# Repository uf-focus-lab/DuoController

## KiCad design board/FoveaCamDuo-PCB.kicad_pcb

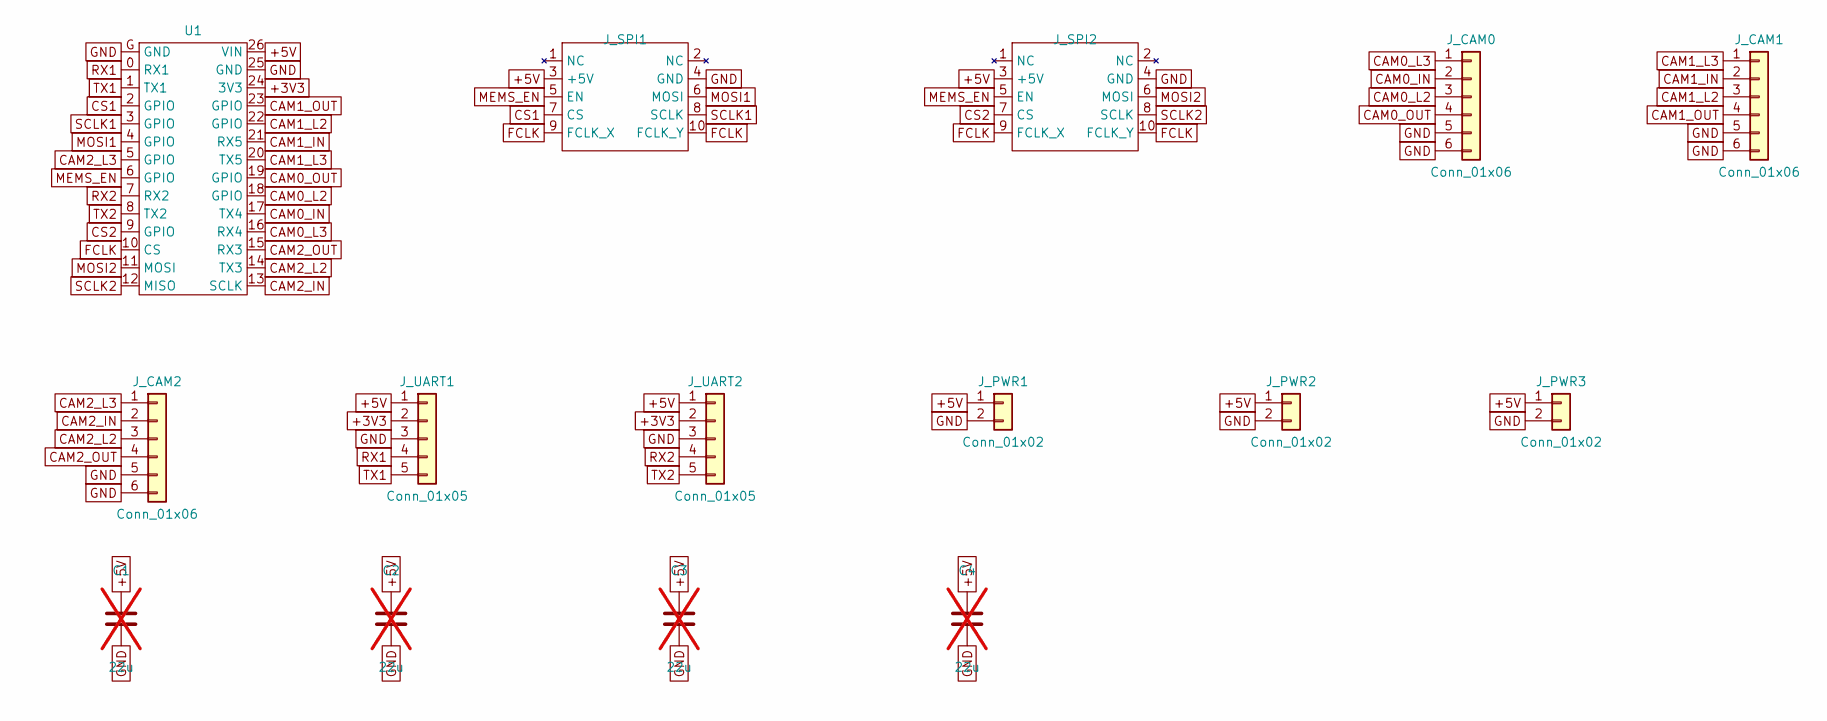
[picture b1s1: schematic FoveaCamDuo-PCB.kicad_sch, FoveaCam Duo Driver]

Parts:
C1, C2, C3, C4: 22u; C_1210_3225Metric_Pad1.33x2.70mm_HandSolder; MPN C3225X7R1E226M250AB; not fitted
J_CAM0, J_CAM1, J_CAM2: Conn_01x06; JST_PH_S6B-PH-K_1x06_P2.00mm_Horizontal_NoSilkScreen; MPN S6B-PH-K-S
J_PWR1, J_PWR2: Conn_01x02; JST_PH_S2B-PH-K_1x02_P2.00mm_Horizontal_NoSilkScreen; MPN S2B-PH-K-S
J_PWR3: Conn_01x02; JST_PH_B2B-PH-K_1x02_P2.00mm_Vertical_NoSilkScreen; MPN B2B-PH-K-S
J_SPI1, J_SPI2: PinHeader_1x10_P1.27mm_Horizontal_Box; MPN 3220-10-0200-00
J_UART1, J_UART2: Conn_01x05; JST_PH_B5B-PH-K_1x05_P2.00mm_Vertical_NoSilkScreen; MPN B5B-PH-K-S
U1: Teensy_4_0; MPN Teensy 4.0

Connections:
+3V3: J_UART1.2, J_UART2.2, U1.24 (3V3)
+5V: C1.1, C2.1, C3.1, C4.1, J_PWR1.1, J_PWR2.1, J_PWR3.1, J_SPI1.3 (+5V), J_SPI2.3 (+5V), J_UART1.1, J_UART2.1, U1.26 (VIN)
CAM0_IN: J_CAM0.2, U1.17 (TX4)
CAM0_L2: J_CAM0.3, U1.18 (GPIO)
CAM0_L3: J_CAM0.1, U1.16 (RX4)
CAM0_OUT: J_CAM0.4, U1.19 (GPIO)
CAM1_IN: J_CAM1.2, U1.21 (RX5)
CAM1_L2: J_CAM1.3, U1.22 (GPIO)
CAM1_L3: J_CAM1.1, U1.20 (TX5)
CAM1_OUT: J_CAM1.4, U1.23 (GPIO)
CAM2_IN: J_CAM2.2, U1.13 (SCLK)
CAM2_L2: J_CAM2.3, U1.14 (TX3)
CAM2_L3: J_CAM2.1, U1.5 (GPIO)
CAM2_OUT: J_CAM2.4, U1.15 (RX3)
CS1: J_SPI1.7 (CS), U1.2 (GPIO)
CS2: J_SPI2.7 (CS), U1.9 (GPIO)
FCLK: J_SPI1.9 (FCLK_X), J_SPI1.10 (FCLK_Y), J_SPI2.9 (FCLK_X), J_SPI2.10 (FCLK_Y), U1.10 (CS)
GND: C1.2, C2.2, C3.2, C4.2, J_CAM0.5, J_CAM0.6, J_CAM1.5, J_CAM1.6, J_CAM2.5, J_CAM2.6, J_PWR1.2, J_PWR2.2, J_PWR3.2, J_SPI1.4 (GND), J_SPI2.4 (GND), J_UART1.3, J_UART2.3, U1.25 (GND), U1.G (GND)
MEMS_EN: J_SPI1.5 (EN), J_SPI2.5 (EN), U1.6 (GPIO)
MOSI1: J_SPI1.6 (MOSI), U1.4 (GPIO)
MOSI2: J_SPI2.6 (MOSI), U1.11 (MOSI)
RX1: J_UART1.4, U1.0 (RX1)
RX2: J_UART2.4, U1.7 (RX2)
SCLK1: J_SPI1.8 (SCLK), U1.3 (GPIO)
SCLK2: J_SPI2.8 (SCLK), U1.12 (MISO)
TX1: J_UART1.5, U1.1 (TX1)
TX2: J_UART2.5, U1.8 (TX2)

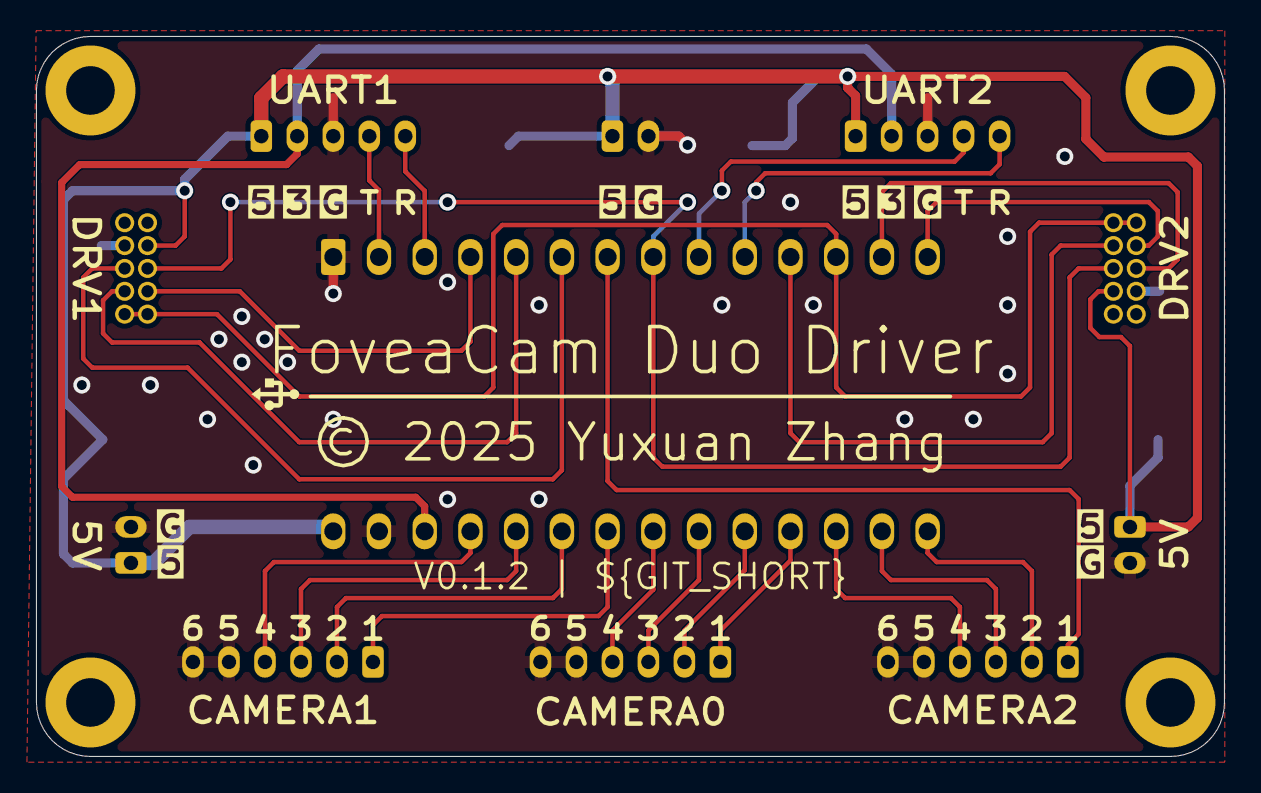
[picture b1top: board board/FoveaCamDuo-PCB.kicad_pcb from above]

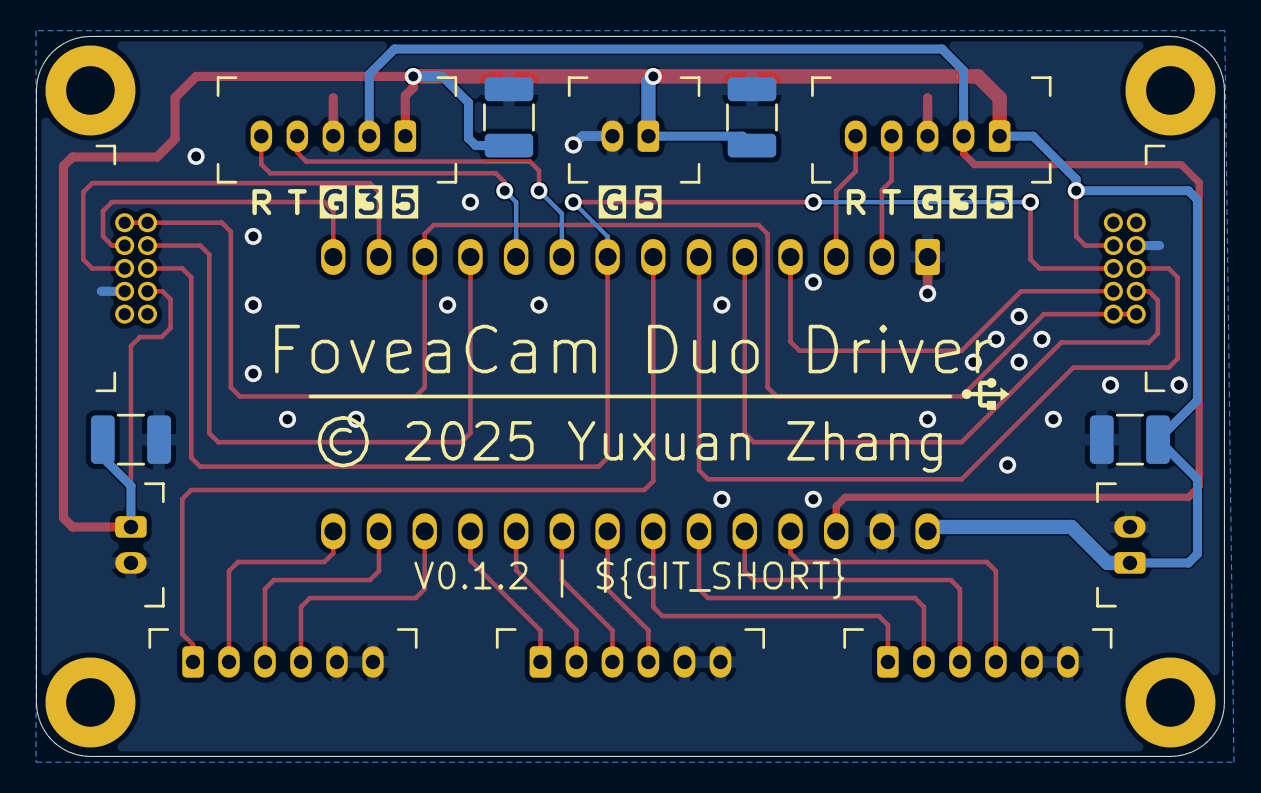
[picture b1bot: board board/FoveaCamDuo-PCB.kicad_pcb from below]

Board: 2 copper layers, 66.0 x 40.0 mm, 19 parts (15 on the bottom side), 27 nets.

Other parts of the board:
MH1, MH2, MH3, MH4: M2.5; MountingHole_2.7mm_M2.5_Pad5.0

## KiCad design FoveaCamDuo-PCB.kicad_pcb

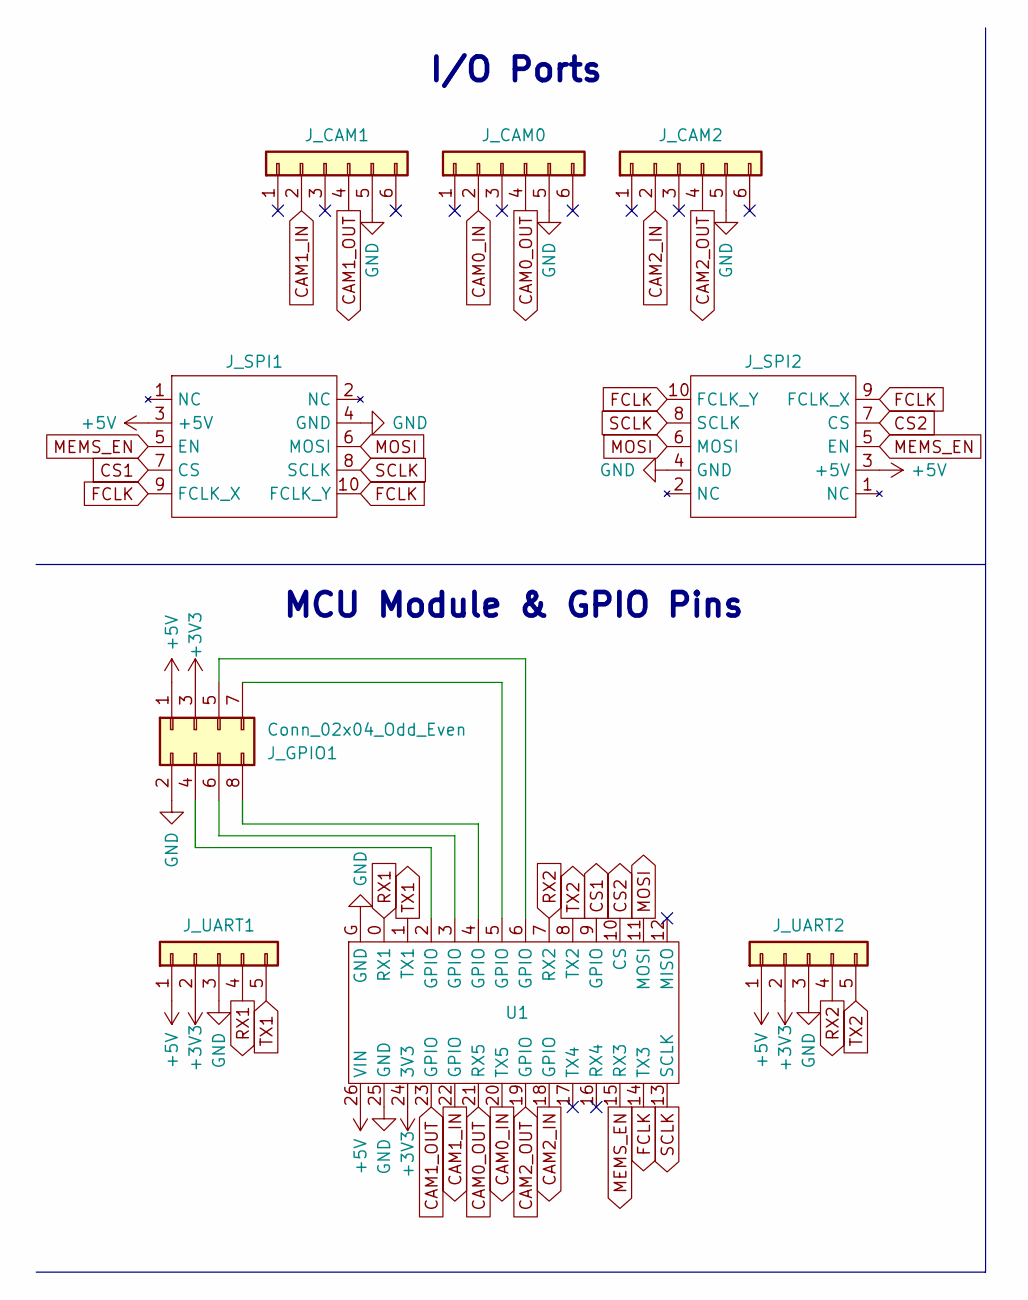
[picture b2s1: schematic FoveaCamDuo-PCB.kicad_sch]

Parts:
J_CAM0, J_CAM1, J_CAM2: Conn_01x06; JST_PH_S6B-PH-K_1x06_P2.00mm_Horizontal_NoSilkScreen
J_GPIO1: Conn_02x04_Odd_Even; PinHeader_2x04_P2.54mm_Vertical_NoSilkScreen
J_SPI1, J_SPI2: PinHeader_1x10_P1.27mm_Horizontal_Box
J_UART1, J_UART2: Conn_01x05; JST_XH_B5B-XH-A_1x05_P2.50mm_Vertical_NoSilkScreen
U1: Teensy_4_0

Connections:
+3V3: J_GPIO1.3, J_UART1.2, J_UART2.2, U1.24 (3V3)
+5V: J_GPIO1.1, J_SPI1.3 (+5V), J_SPI2.3 (+5V), J_UART1.1, J_UART2.1, U1.26 (VIN)
CAM0_IN: J_CAM0.2, U1.20 (TX5)
CAM0_OUT: J_CAM0.4, U1.21 (RX5)
CAM1_IN: J_CAM1.2, U1.22 (GPIO)
CAM1_OUT: J_CAM1.4, U1.23 (GPIO)
CAM2_IN: J_CAM2.2, U1.18 (GPIO)
CAM2_OUT: J_CAM2.4, U1.19 (GPIO)
CS1: J_SPI1.7 (CS), U1.9 (GPIO)
CS2: J_SPI2.7 (CS), U1.10 (CS)
FCLK: J_SPI1.9 (FCLK_X), J_SPI1.10 (FCLK_Y), J_SPI2.9 (FCLK_X), J_SPI2.10 (FCLK_Y), U1.14 (TX3)
GND: J_CAM0.5, J_CAM1.5, J_CAM2.5, J_GPIO1.2, J_SPI1.4 (GND), J_SPI2.4 (GND), J_UART1.3, J_UART2.3, U1.25 (GND), U1.G (GND)
MEMS_EN: J_SPI1.5 (EN), J_SPI2.5 (EN), U1.15 (RX3)
MOSI: J_SPI1.6 (MOSI), J_SPI2.6 (MOSI), U1.11 (MOSI)
unnamed: J_GPIO1.4, U1.2 (GPIO)
unnamed: J_GPIO1.5, U1.6 (GPIO)
unnamed: J_GPIO1.6, U1.3 (GPIO)
unnamed: J_GPIO1.7, U1.5 (GPIO)
unnamed: J_GPIO1.8, U1.4 (GPIO)
RX1: J_UART1.4, U1.0 (RX1)
RX2: J_UART2.4, U1.7 (RX2)
SCLK: J_SPI1.8 (SCLK), J_SPI2.8 (SCLK), U1.13 (SCLK)
TX1: J_UART1.5, U1.1 (TX1)
TX2: J_UART2.5, U1.8 (TX2)

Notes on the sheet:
MCU Module & GPIO Pins
I/O Ports

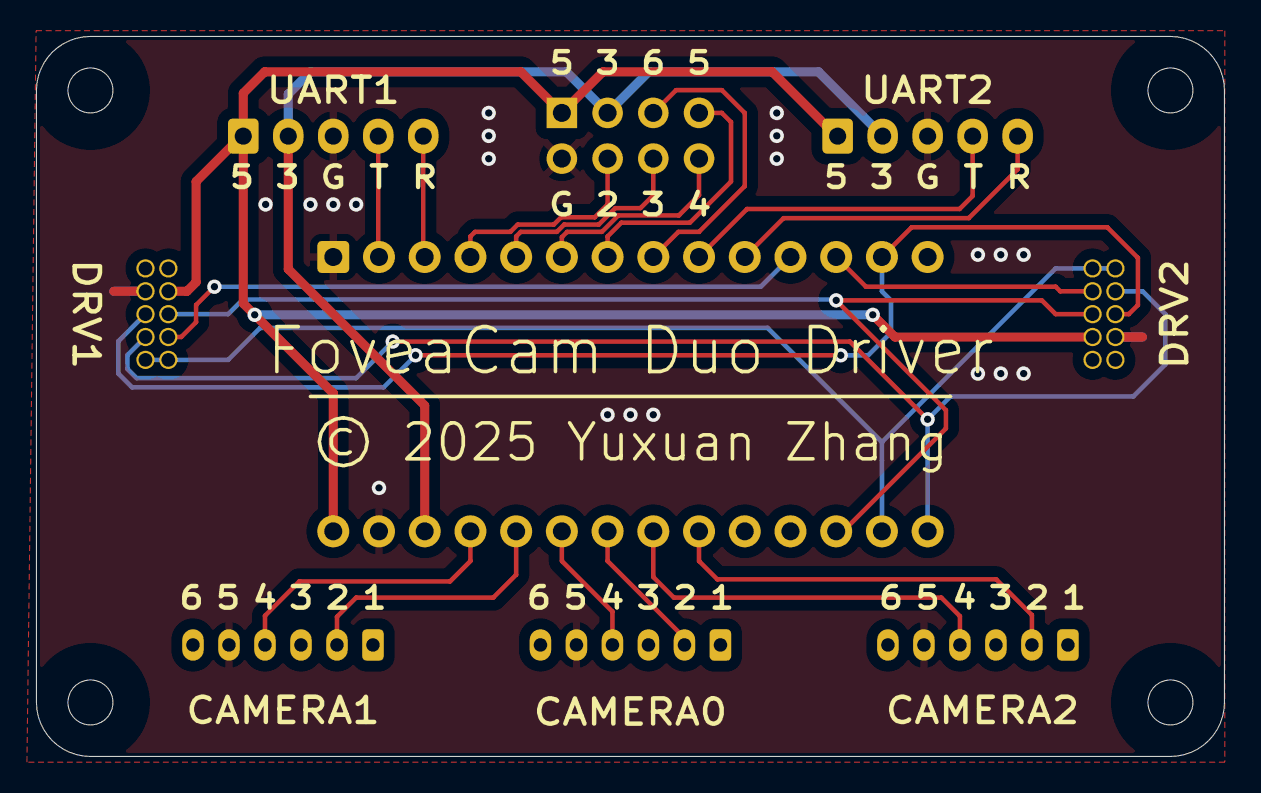
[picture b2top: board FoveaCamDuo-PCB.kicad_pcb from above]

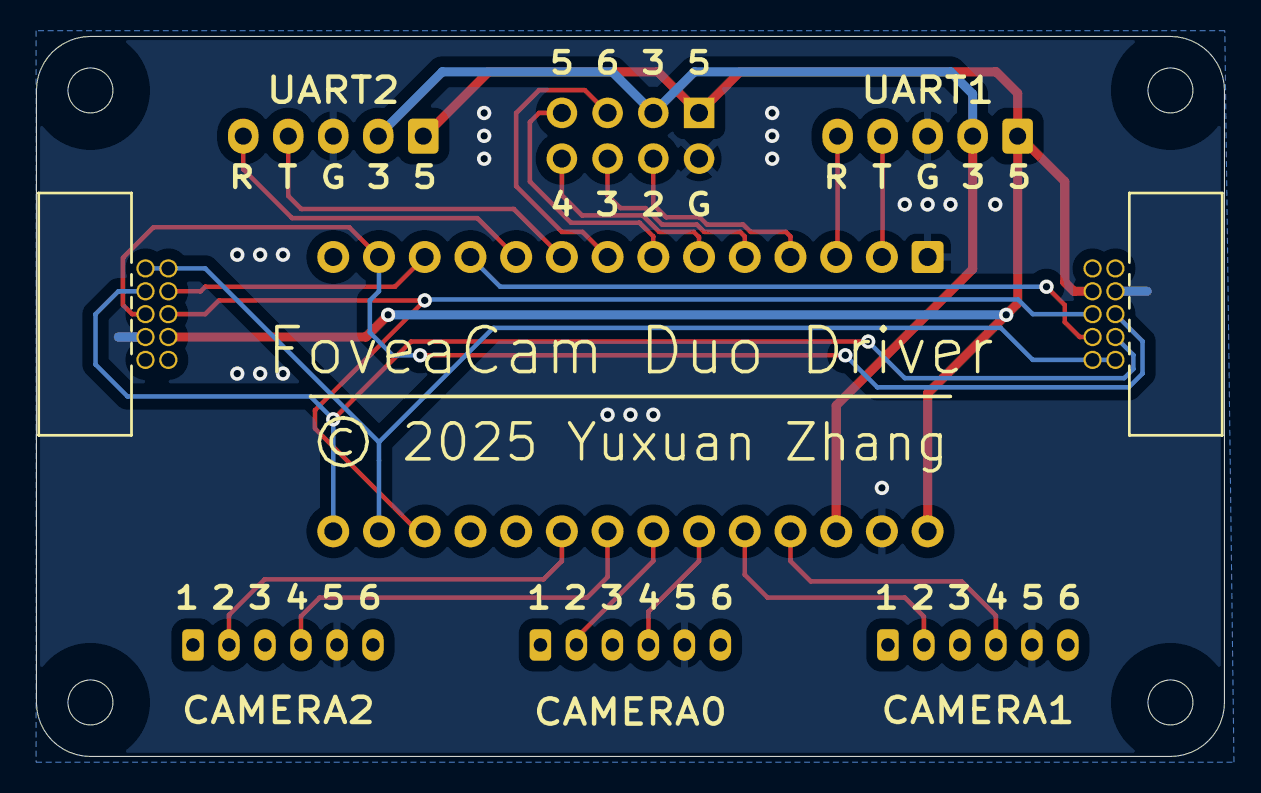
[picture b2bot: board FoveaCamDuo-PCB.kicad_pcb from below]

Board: 2 copper layers, 66.0 x 40.0 mm, 9 parts (9 on the bottom side), 24 nets.

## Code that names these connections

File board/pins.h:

/* FoveaCam Duo Driver: Teensy 4.0 pin map.
 *
 * GENERATED by tools/gen_pins.py from board/netlist.py (sha1 770d2c06a77e); do not edit.
 * Numbers are Teensy digital pin numbers (pinMode / digitalWrite).
 */
#ifndef FOVEACAM_DUO_PINS_H
#define FOVEACAM_DUO_PINS_H

#define PIN_RX1       0   /* RX1: J_UART1.4 */
#define PIN_TX1       1   /* TX1: J_UART1.5 */
#define PIN_CS1       2   /* CS1: J_SPI1.7 */
#define PIN_SCLK1     3   /* SCLK1: J_SPI1.8 */
#define PIN_MOSI1     4   /* MOSI1: J_SPI1.6 */
#define PIN_CAM2_L3   5   /* CAM2_L3: J_CAM2.1 */
#define PIN_MEMS_EN   6   /* MEMS_EN: J_SPI1.5, J_SPI2.5 */
#define PIN_RX2       7   /* RX2: J_UART2.4 */
#define PIN_TX2       8   /* TX2: J_UART2.5 */
#define PIN_CS2       9   /* CS2: J_SPI2.7 */
#define PIN_FCLK     10   /* FCLK: J_SPI1.10, J_SPI1.9, J_SPI2.10, J_SPI2.9 */
#define PIN_MOSI2    11   /* MOSI2: J_SPI2.6 */
#define PIN_SCLK2    12   /* SCLK2: J_SPI2.8 */
#define PIN_CAM2_IN  13   /* CAM2_IN: J_CAM2.2 */
#define PIN_CAM2_L2  14   /* CAM2_L2: J_CAM2.3 */
#define PIN_CAM2_OUT 15   /* CAM2_OUT: J_CAM2.4 */
#define PIN_CAM0_L3  16   /* CAM0_L3: J_CAM0.1 */
#define PIN_CAM0_IN  17   /* CAM0_IN: J_CAM0.2 */
#define PIN_CAM0_L2  18   /* CAM0_L2: J_CAM0.3 */
#define PIN_CAM0_OUT 19   /* CAM0_OUT: J_CAM0.4 */
#define PIN_CAM1_L3  20   /* CAM1_L3: J_CAM1.1 */
#define PIN_CAM1_IN  21   /* CAM1_IN: J_CAM1.2 */
#define PIN_CAM1_L2  22   /* CAM1_L2: J_CAM1.3 */
#define PIN_CAM1_OUT 23   /* CAM1_OUT: J_CAM1.4 */

/* Level read on PIN_CAMn_OUT while camera n exposes: the camera's
 * opto output (open collector) pulls the line LOW against the
 * Teensy's internal pull-up (INPUT_PULLUP); no receiver on the board. */
#define STROBE_ACTIVE_LEVEL LOW

/* Firmware notes (board/netlist.py FIRMWARE_NOTES):
 * Buses: DRV1 = FlexIO1 (SCLK1 3 = FlexIO1 D05, MOSI1 4 = D06), DRV2 =
 * FlexIO2 (SCLK2 12 = D01, MOSI2 11 = D02); CS1 / CS2 plain GPIO.  [Teensyduino
 * 1.159 FlexIO_t4.cpp flex1_hardware / flex2_hardware, Teensy 4.0 section]
 * AD5664R frame: 24 bits, data taken on the SCLK falling edge (SPI mode 1
 * or 2), SYNC low for the whole frame.  [Mirrorcle MEMS Drivers 5.x guide
 * p26, p42]  Init per power-up: 0x280001, 0x380001, 0x20000F, 0x300000 (p26).
 * Pads (IOMUXC SW_PAD_CTL): SCLKn / MOSIn / CSn DSE 1..3 (150..50 ohm),
 * SRE 0 (slow), SPEED 0; FCLK DSE 1, SRE 0.  The guide warns of crosstalk
 * from fast FCLK / SPI edges and asks for reduced slew rates (p10).
 * [i.MX RT1060 reference manual, IOMUXC SW_PAD_CTL_PAD_* fields]
 * MEMS_EN (6 = GPIO_B0_10): 100 k pull-down during reset, keeper after it
 * [i.MX RT1060 datasheet Rev. 4, Table 83, PDF p95; boot pins p85].  Drive
 * it LOW first thing in setup(); raise it only after the DAC init, Vbias on
 * all channels and FCLK running; drop it before stopping SPI or FCLK
 * [guide p27 steps 1-5, p31].  It enables both drivers (shared).
 * FCLK (10, PWM): 50 % square wave at 60 x the filter cut-off, 3 kHz..3 MHz,
 * one clock for both drivers and both axes [guide p14, p16, p41].
 * Line3 (CAMn_L3: 5, 16, 20): keep INPUT (high-Z) from boot; drive only
 * after the camera's Line3 is set as an input (Line3 is also the camera's
 * 8-24 V VAUX input; a Teensy pin is 3.6 V abs. max).
 * Strobes (CAMn_OUT: 23, 19, 15): INPUT_PULLUP, active LOW; any pin can
 * attachInterrupt.  Triggers (CAMn_IN: 21, 17, 13) are outputs; pin 13
 * also drives the Teensy LED (it lights with the camera 2 trigger).
 * No spare pin: an enable per driver is wanted (owner 2026-10-07) once a
 * GPIO is free in a later revision.
 */

#endif /* FOVEACAM_DUO_PINS_H */

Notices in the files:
FoveaCamDuo-PCB.kicad_pcb:
© 2025 Yuxuan Zhang
